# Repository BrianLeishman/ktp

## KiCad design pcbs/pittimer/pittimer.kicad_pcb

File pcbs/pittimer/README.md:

# jrgbwww24 - esp8266 board for controlling RGB W WW 24V LED strips

This PCB is designed to take esp8266 NodeMCU boards and allow them to control 24V LED strips that have RGB, cool white, and warm white LEDs.

This board is also designed to power the esp8266 board with 5V, so no USB connection is needed. Another cool feature is that this board has a 5V fan header (like a computer motherboard would), so you can plug in a fan like [this Noctua one](https://amzn.to/3mTPDOA) in case some cooling is needed.

PCB dimensions and screw holes are designed to be an exact match to a Raspberry Pi 4, for compatibility with Pi accessories like enclosures or cases.

## Heads up!

The circuits for each color channel are inverted, so make sure you specify `inverted: True` in your esphome config, for example. You can check a full example config [below](#example-esphome-config).

# Renders

# Example esphome config

```yaml
esphome:
  name: kitchen-under-cabinet-1
  platform: ESP8266
  board: nodemcuv2

# Enable logging
logger:

# Enable Home Assistant API
api:
  password: "mypassword"

ota:
  password: "mypassword"

wifi:
  ssid: "My Internet"
  password: "wifi password"
  manual_ip:
    static_ip: 192.168.1.50
    gateway: 192.168.1.1
    subnet: 255.255.255.0

  # Enable fallback hotspot (captive portal) in case wifi connection fails
  ap:
    ssid: "Rgbww Fallback Hotspot"
    password: "ZiNHD3xPr345s7UL"

captive_portal:

#RGB CoolWhite WarmWhite
output:
  - platform: esp8266_pwm
    pin: 4
    frequency: 1000 Hz
    id: pwm_r
    inverted: True
  - platform: esp8266_pwm
    pin: 14
    frequency: 1000 Hz
    id: pwm_g
    inverted: True
  - platform: esp8266_pwm
    pin: 12
    frequency: 1000 Hz
    id: pwm_b
    inverted: True
  - platform: esp8266_pwm
    pin: 13
    frequency: 1000 Hz
    id: pwm_cw
    inverted: True
  - platform: esp8266_pwm
    pin: 15
    frequency: 1000 Hz
    id: pwm_ww
    inverted: True
light:
  - platform: rgbww
    name: "K Light"
    red: pwm_r
    green: pwm_g
    blue: pwm_b
    cold_white: pwm_cw
    warm_white: pwm_ww
    cold_white_color_temperature: 6500 K
    warm_white_color_temperature: 3000 K
    color_interlock: True
```

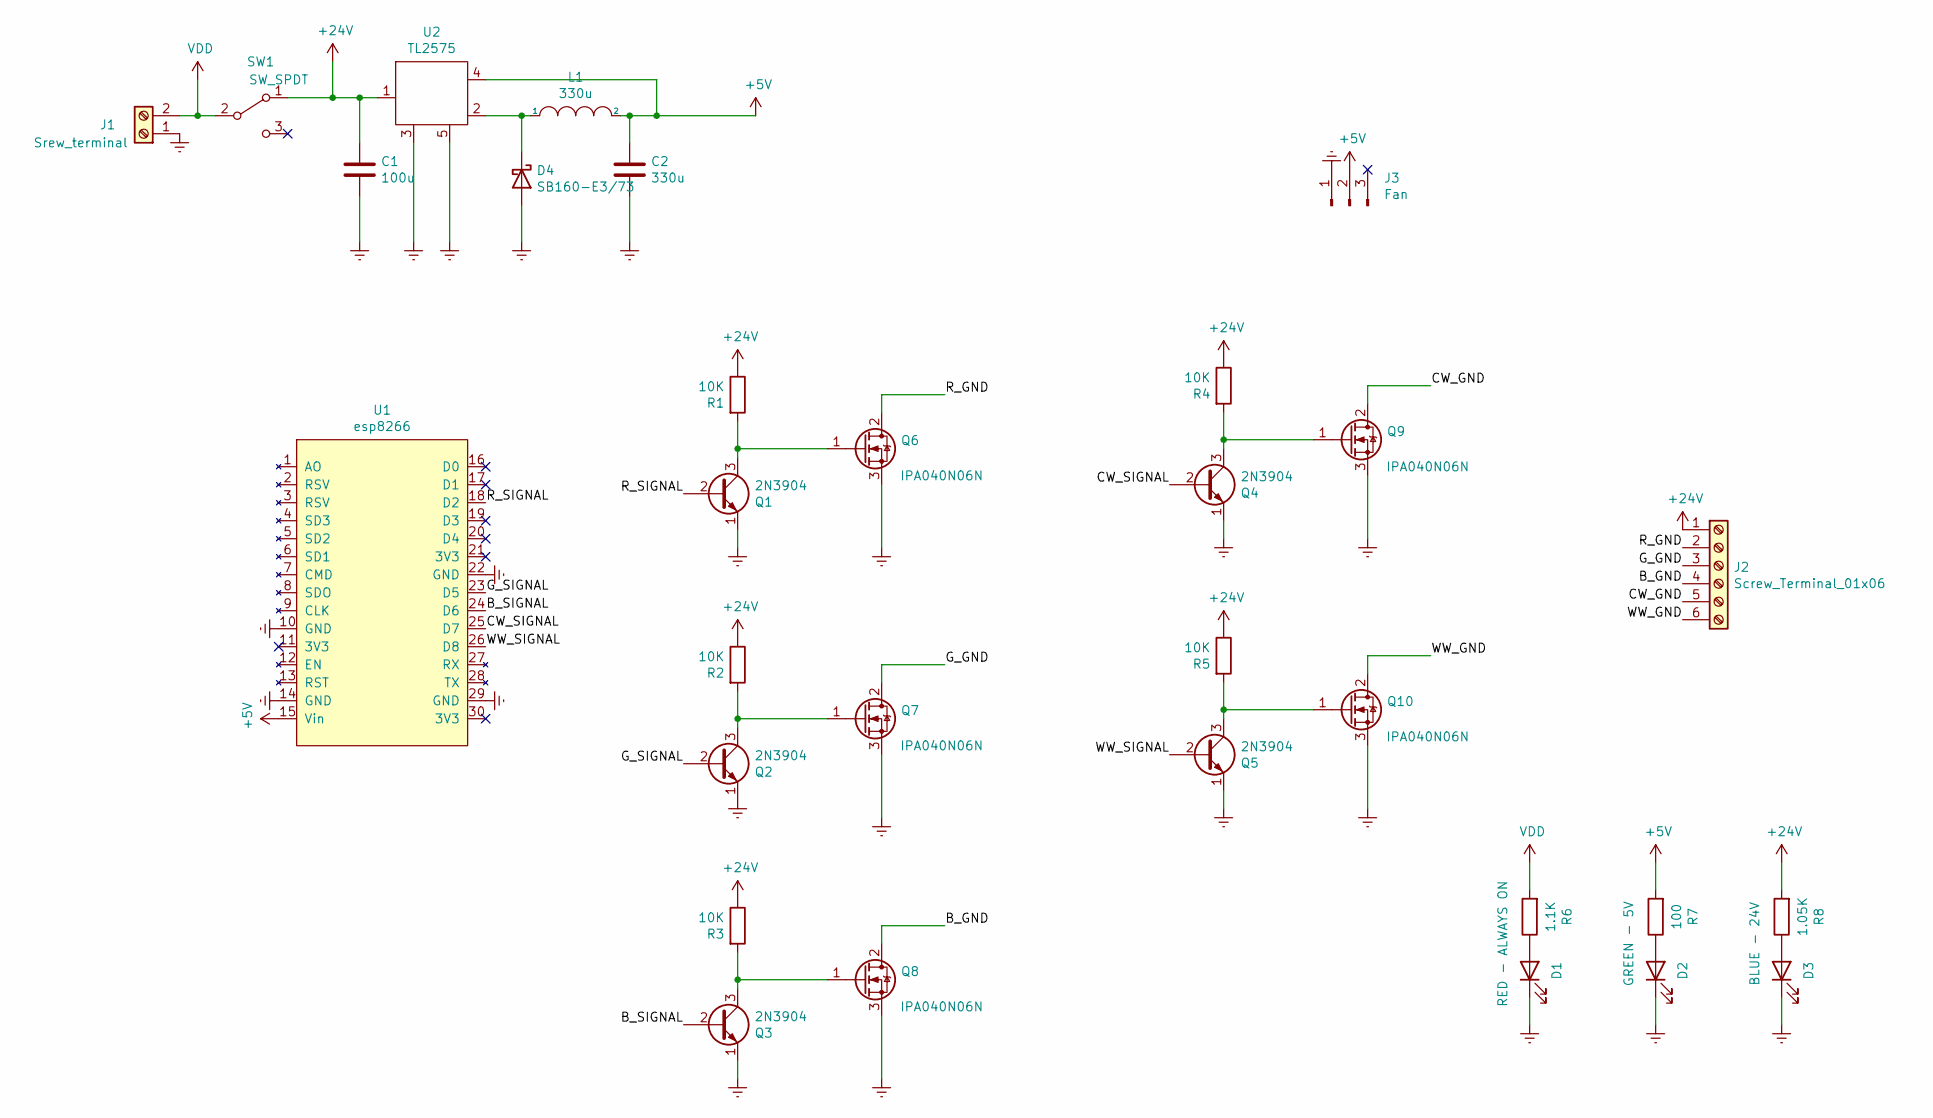
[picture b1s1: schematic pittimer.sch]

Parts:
C1: 100u; CP_Radial_D5.0mm_P2.00mm
C2: 330u; CP_Radial_D5.0mm_P2.00mm
D1: RED - ALWAYS ON; LED_1206_3216Metric
D2: GREEN - 5V; LED_1206_3216Metric
D3: BLUE - 24V; LED_1206_3216Metric
D4: SB160-E3/73; D_DO-41_SOD81_P7.62mm_Horizontal
J1: Srew_terminal; TerminalBlock_bornier-2_P5.08mm
J2: Screw_Terminal_01x06; TerminalBlock_bornier-6_P5.08mm
J3: Fan; FanPinHeader_1x03_P2.54mm_Vertical
L1: 330u; L_Wuerth_WE-PD-Typ-LS_Handsoldering
Q1, Q2, Q3, Q4, Q5: 2N3904; TO-92_Inline
Q6, Q7, Q8, Q9, Q10: IPA040N06N; TO-220F-3_Vertical
R1, R2, R3, R4, R5: 10K; R_Axial_DIN0207_L6.3mm_D2.5mm_P7.62mm_Horizontal
R6: 1.1K; R_Axial_DIN0207_L6.3mm_D2.5mm_P7.62mm_Horizontal
R7: 100; R_Axial_DIN0207_L6.3mm_D2.5mm_P7.62mm_Horizontal
R8: 1.05K; R_Axial_DIN0207_L6.3mm_D2.5mm_P7.62mm_Horizontal
SW1: SW_SPDT; 1P2T SPDT
U1: esp8266; KeeYees ESP8266 ESP-12E
U2: TL2575; TO-220-5_Horizontal_TabDown

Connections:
+5V: C2.1, J3.2, L1.2, R7.2, U1.15 (Vin), U2.4
+24V: C1.1, J2.1, R1.1, R2.1, R3.1, R4.1, R5.1, R8.2, SW1.1 (A), U2.1
/B_GND: J2.4, Q8.2 (D)
/B_SIGNAL: Q3.2 (B), U1.24 (D6)
/CW_GND: J2.5, Q9.2 (D)
/CW_SIGNAL: Q4.2 (B), U1.25 (D7)
/G_GND: J2.3, Q7.2 (D)
/G_SIGNAL: Q2.2 (B), U1.23 (D5)
/R_GND: J2.2, Q6.2 (D)
/R_SIGNAL: Q1.2 (B), U1.18 (D2)
/WW_GND: J2.6, Q10.2 (D)
/WW_SIGNAL: Q5.2 (B), U1.26 (D8)
Earth: C1.2, C2.2, D1.1 (K), D2.1 (K), D3.1 (K), D4.2 (A), J1.1, J3.1, Q1.1 (E), Q2.1 (E), Q3.1 (E), Q4.1 (E), Q5.1 (E), Q6.3 (S), Q6.5 (S), Q6.6 (S), Q6.7 (S), Q7.3 (S), Q7.5 (S), Q7.6 (S), Q7.7 (S), Q8.3 (S), Q8.5 (S), Q8.6 (S), Q8.7 (S), Q9.3 (S), Q9.5 (S), Q9.6 (S), Q9.7 (S), Q10.3 (S), Q10.5 (S), Q10.6 (S), Q10.7 (S), U1.10 (GND), U1.14 (GND), U1.22 (GND), U1.29 (GND), U2.3, U2.5
unnamed: D1.2 (A), R6.1
unnamed: D2.2 (A), R7.1
unnamed: D3.2 (A), R8.1
unnamed: D4.1 (K), L1.1, U2.2
unnamed: Q1.3 (C), Q6.1 (G), R1.2
unnamed: Q2.3 (C), Q7.1 (G), R2.2
unnamed: Q3.3 (C), Q8.1 (G), R3.2
unnamed: Q4.3 (C), Q9.1 (G), R4.2
unnamed: Q5.3 (C), Q10.1 (G), R5.2
VDD: J1.2, R6.2, SW1.2 (B)

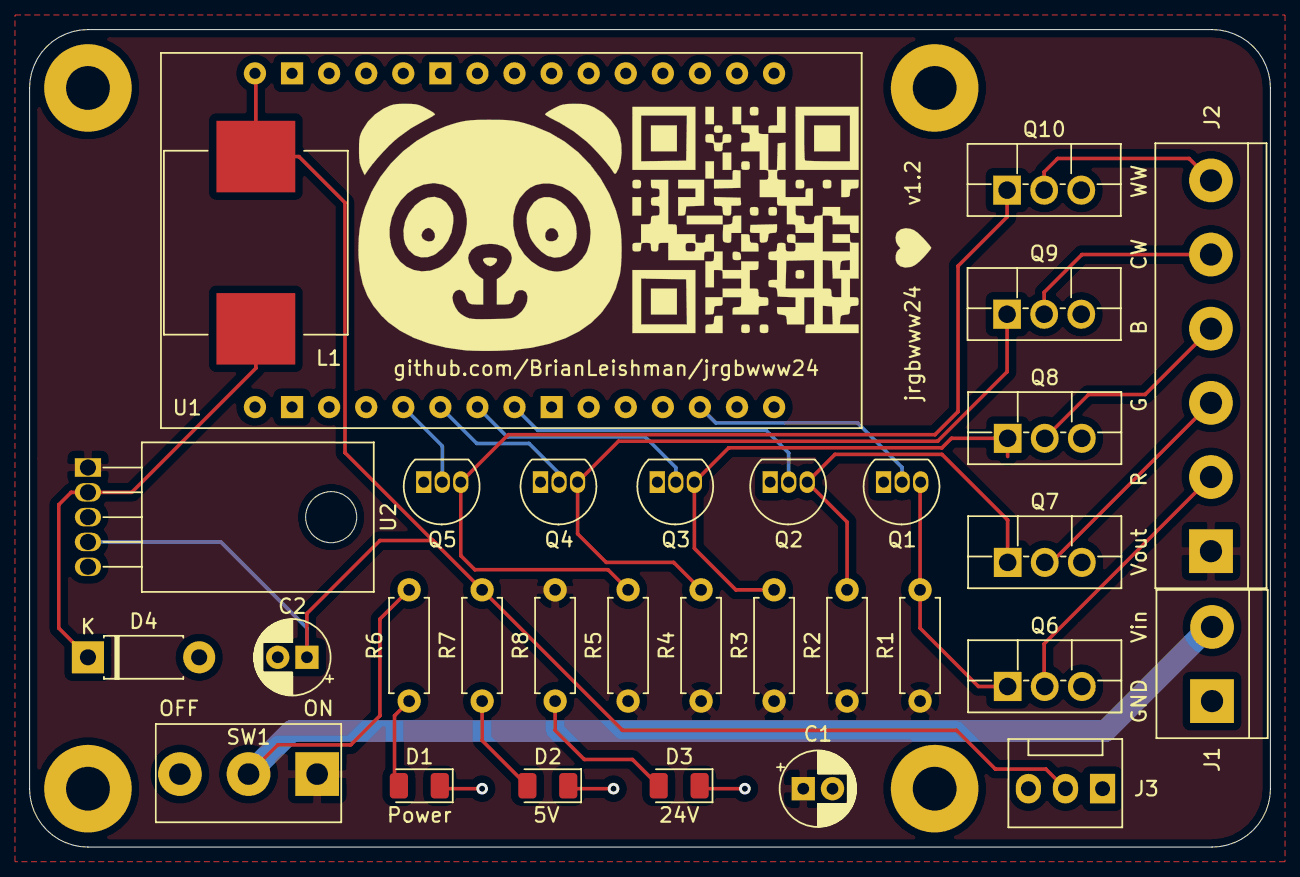
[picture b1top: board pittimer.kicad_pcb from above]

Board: 2 copper layers, 85.0 x 56.0 mm, 31 parts (0 on the bottom side), 23 nets.

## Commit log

2023-11-02 clone jrgbwww
2023-11-02 remove autosave
2023-11-02 driver test code
